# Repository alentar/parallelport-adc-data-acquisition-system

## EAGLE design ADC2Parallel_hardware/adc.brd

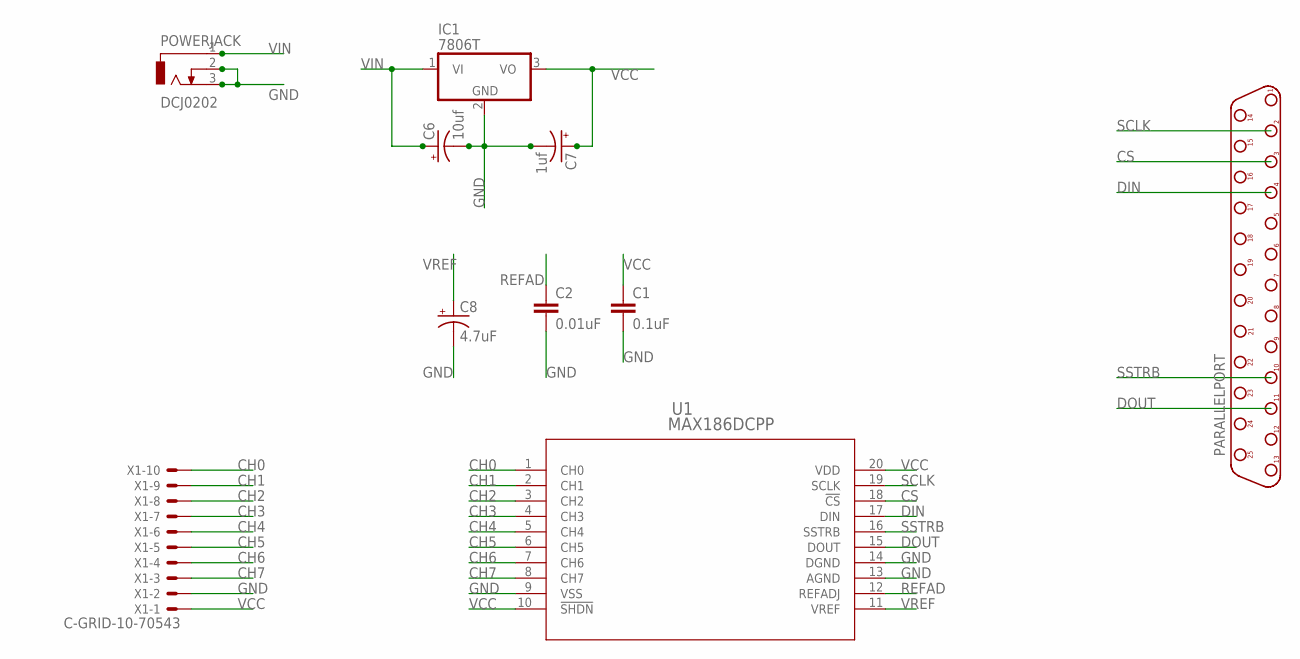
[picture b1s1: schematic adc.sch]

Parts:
C1: 0.1uF; C050-035X075
C2: 0.01uF; C050-035X075; MPN B32529C1103J189
C6: 10uf; E2-5
C7: 1uf; E2-5
C8: 4.7uF; E2-5
IC1: 7806T; TO220H
PARALLELPORT: DB25F; D-25F
POWERJACK: DCJ0202
U1: MAX186DCPP; 21-0043D_20
X1: C-GRID-10-70543; 70543-10

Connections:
CH0: U1.1 (CH0), X1.10
CH1: U1.2 (CH1), X1.9
CH2: U1.3 (CH2), X1.8
CH3: U1.4 (CH3), X1.7
CH4: U1.5 (CH4), X1.6
CH5: U1.6 (CH5), X1.5
CH6: U1.7 (CH6), X1.4
CH7: U1.8 (CH7), X1.3
CS: PARALLELPORT.3, U1.18 (!CS)
DIN: PARALLELPORT.4, U1.17 (DIN)
DOUT: PARALLELPORT.11, U1.15 (DOUT)
GND: C1.2, C2.2, C6.-, C7.-, C8.-, IC1.2 (GND), POWERJACK.2, POWERJACK.3, U1.9 (VSS), U1.13 (AGND), U1.14 (DGND), X1.2
REFAD: C2.1, U1.12 (REFADJ)
SCLK: PARALLELPORT.2, U1.19 (SCLK)
SSTRB: PARALLELPORT.10, U1.16 (SSTRB)
VCC: C1.1, C7.+, IC1.3 (VO), U1.10 (!SHDN), U1.20 (VDD), X1.1
VIN: C6.+, IC1.1 (VI), POWERJACK.1
VREF: C8.+, U1.11 (VREF)

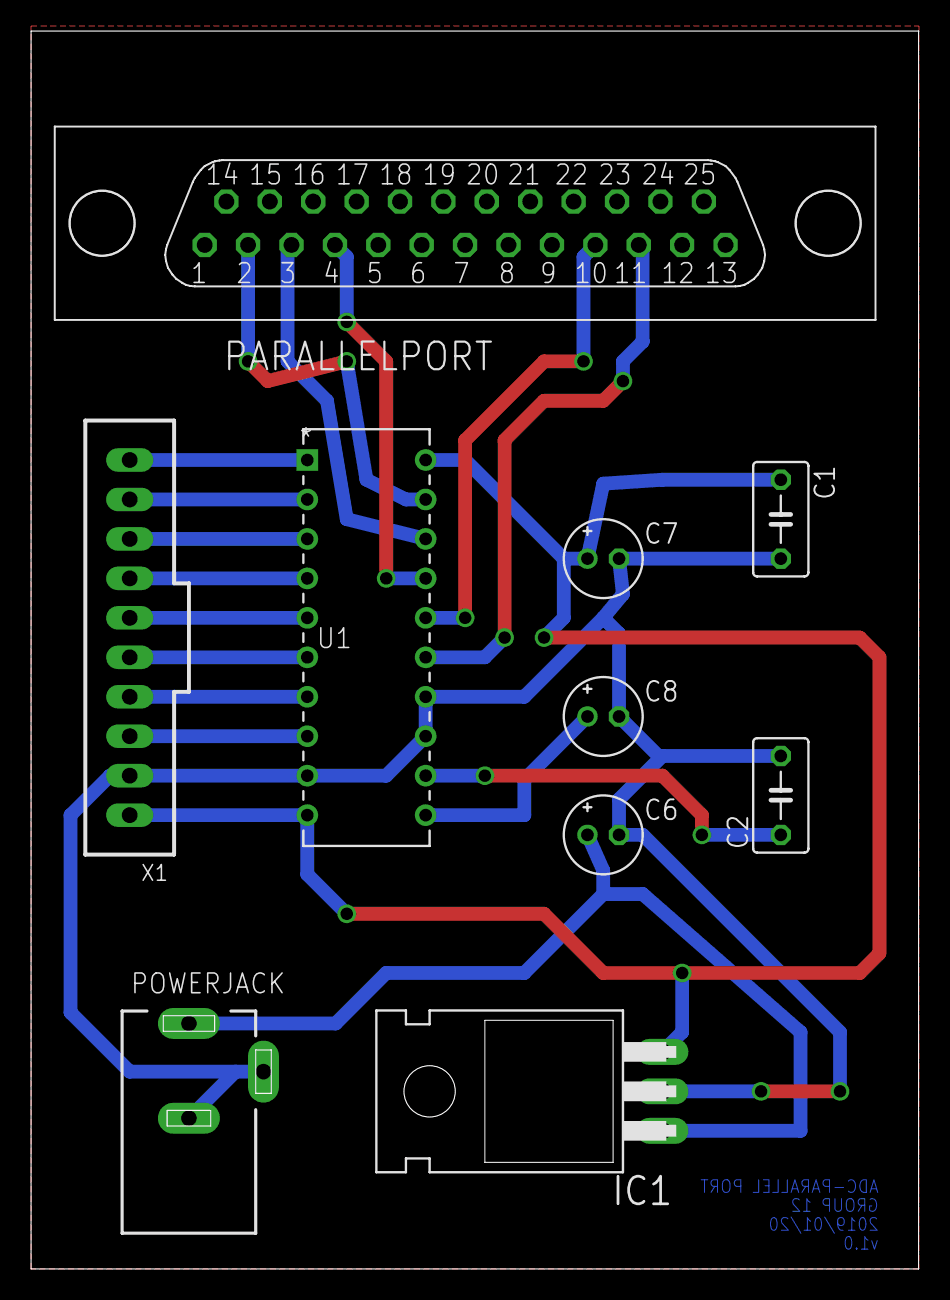
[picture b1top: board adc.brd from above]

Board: 2 copper layers, 57.1 x 79.7 mm, 10 parts (0 on the bottom side), 18 nets.

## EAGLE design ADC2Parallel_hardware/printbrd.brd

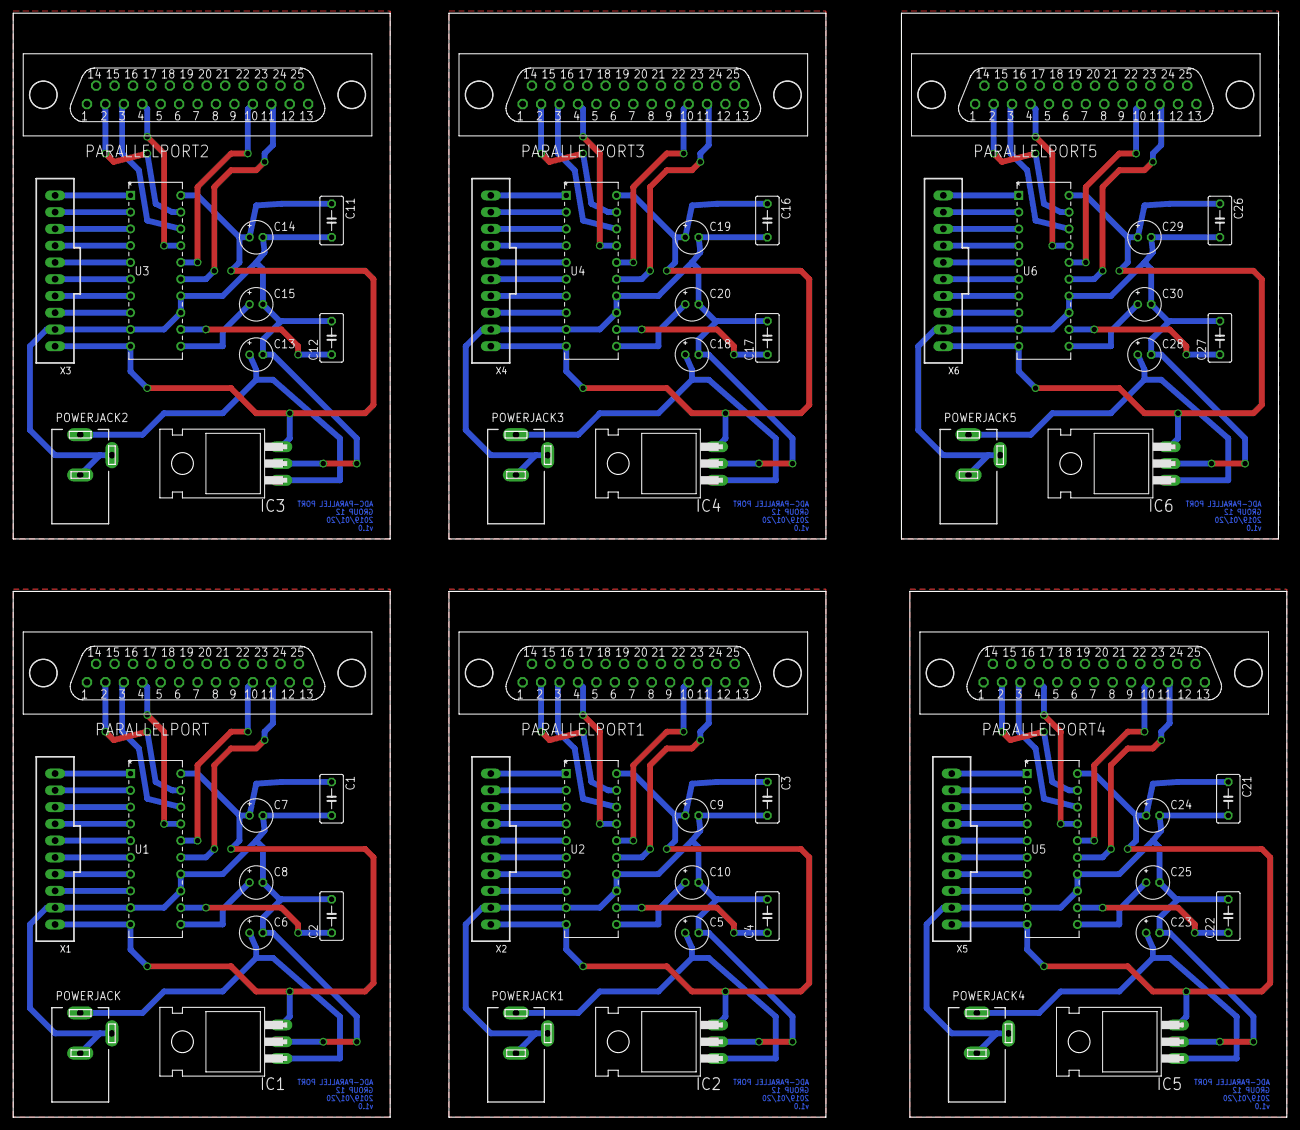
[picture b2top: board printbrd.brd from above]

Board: 2 copper layers, 193.0 x 167.3 mm, 60 parts (0 on the bottom side), 108 nets.

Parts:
C1, C3, C11, C16, C21, C26: 0.1uF; C050-035X075
C2, C4, C12, C17, C22, C27: 0.01uF; C050-035X075
C5, C6, C13, C18, C23, C28: 10uf; E2-5
C7, C9, C14, C19, C24, C29: 1uf; E2-5
C8, C10, C15, C20, C25, C30: 4.7uF; E2-5
IC1, IC2, IC3, IC4, IC5, IC6: 7806T; TO220H
PARALLELPORT, PARALLELPORT1, PARALLELPORT2, PARALLELPORT3, PARALLELPORT4, PARALLELPORT5: D-25F
POWERJACK, POWERJACK1, POWERJACK2, POWERJACK3, POWERJACK4, POWERJACK5: DCJ0202
U1, U2, U3, U4, U5, U6: MAX186DCPP; 21-0043D_20
X1, X2, X3, X4, X5, X6: C-GRID-10-70543; 70543-10

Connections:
CH0: U1.1, X1.10
CH1: U1.2, X1.9
CH2: U1.3, X1.8
CH3: U1.4, X1.7
CH4: U1.5, X1.6
CH5: U1.6, X1.5
CH6: U1.7, X1.4
CH7: U1.8, X1.3
CH8: U2.1, X2.10
CH9: U2.2, X2.9
CH10: U2.3, X2.8
CH11: U2.4, X2.7
CH12: U2.5, X2.6
CH13: U2.6, X2.5
CH14: U2.7, X2.4
CH15: U2.8, X2.3
CH16: U3.1, X3.10
CH17: U3.2, X3.9
CH18: U3.3, X3.8
CH19: U3.4, X3.7
CH20: U3.5, X3.6
CH21: U3.6, X3.5
CH22: U3.7, X3.4
CH23: U3.8, X3.3
CH24: U4.1, X4.10
CH25: U4.2, X4.9
CH26: U4.3, X4.8
CH27: U4.4, X4.7
CH28: U4.5, X4.6
CH29: U4.6, X4.5
CH30: U4.7, X4.4
CH31: U4.8, X4.3
CH32: U5.1, X5.10
CH33: U5.2, X5.9
CH34: U5.3, X5.8
CH35: U5.4, X5.7
CH36: U5.5, X5.6
CH37: U5.6, X5.5
CH38: U5.7, X5.4
CH39: U5.8, X5.3
CH40: U6.1, X6.10
CH41: U6.2, X6.9
CH42: U6.3, X6.8
CH43: U6.4, X6.7
CH44: U6.5, X6.6
CH45: U6.6, X6.5
CH46: U6.7, X6.4
CH47: U6.8, X6.3
CS: PARALLELPORT.3, U1.18
CS1: PARALLELPORT1.3, U2.18
CS2: PARALLELPORT2.3, U3.18
CS3: PARALLELPORT3.3, U4.18
CS4: PARALLELPORT4.3, U5.18
CS5: PARALLELPORT5.3, U6.18
DIN: PARALLELPORT.4, U1.17
DIN1: PARALLELPORT1.4, U2.17
DIN2: PARALLELPORT2.4, U3.17
DIN3: PARALLELPORT3.4, U4.17
DIN4: PARALLELPORT4.4, U5.17
DIN5: PARALLELPORT5.4, U6.17
DOUT: PARALLELPORT.11, U1.15
DOUT1: PARALLELPORT1.11, U2.15
DOUT2: PARALLELPORT2.11, U3.15
DOUT3: PARALLELPORT3.11, U4.15
DOUT4: PARALLELPORT4.11, U5.15
DOUT5: PARALLELPORT5.11, U6.15
GND: C1.2, C2.2, C6.-, C7.-, C8.-, IC1.2, POWERJACK.2, POWERJACK.3, U1.9, U1.13, U1.14, X1.2
GND1: C3.2, C4.2, C5.-, C9.-, C10.-, IC2.2, POWERJACK1.2, POWERJACK1.3, U2.9, U2.13, U2.14, X2.2
GND2: C11.2, C12.2, C13.-, C14.-, C15.-, IC3.2, POWERJACK2.2, POWERJACK2.3, U3.9, U3.13, U3.14, X3.2
GND3: C16.2, C17.2, C18.-, C19.-, C20.-, IC4.2, POWERJACK3.2, POWERJACK3.3, U4.9, U4.13, U4.14, X4.2
GND4: C21.2, C22.2, C23.-, C24.-, C25.-, IC5.2, POWERJACK4.2, POWERJACK4.3, U5.9, U5.13, U5.14, X5.2
GND5: C26.2, C27.2, C28.-, C29.-, C30.-, IC6.2, POWERJACK5.2, POWERJACK5.3, U6.9, U6.13, U6.14, X6.2
REFAD: C2.1, U1.12
REFAD1: C4.1, U2.12
REFAD2: C12.1, U3.12
REFAD3: C17.1, U4.12
REFAD4: C22.1, U5.12
REFAD5: C27.1, U6.12
SCLK: PARALLELPORT.2, U1.19
SCLK1: PARALLELPORT1.2, U2.19
SCLK2: PARALLELPORT2.2, U3.19
SCLK3: PARALLELPORT3.2, U4.19
SCLK4: PARALLELPORT4.2, U5.19
SCLK5: PARALLELPORT5.2, U6.19
SSTRB: PARALLELPORT.10, U1.16
SSTRB1: PARALLELPORT1.10, U2.16
SSTRB2: PARALLELPORT2.10, U3.16
SSTRB3: PARALLELPORT3.10, U4.16
SSTRB4: PARALLELPORT4.10, U5.16
SSTRB5: PARALLELPORT5.10, U6.16
VCC: C1.1, C7.+, IC1.3, U1.10, U1.20, X1.1
VCC1: C3.1, C9.+, IC2.3, U2.10, U2.20, X2.1
VCC2: C11.1, C14.+, IC3.3, U3.10, U3.20, X3.1
VCC3: C16.1, C19.+, IC4.3, U4.10, U4.20, X4.1
VCC4: C21.1, C24.+, IC5.3, U5.10, U5.20, X5.1
VCC5: C26.1, C29.+, IC6.3, U6.10, U6.20, X6.1
VIN: C6.+, IC1.1, POWERJACK.1
VIN1: C5.+, IC2.1, POWERJACK1.1
VIN2: C13.+, IC3.1, POWERJACK2.1
VIN3: C18.+, IC4.1, POWERJACK3.1
VIN4: C23.+, IC5.1, POWERJACK4.1
VIN5: C28.+, IC6.1, POWERJACK5.1
VREF: C8.+, U1.11
VREF1: C10.+, U2.11
VREF2: C15.+, U3.11
VREF3: C20.+, U4.11
VREF4: C25.+, U5.11
VREF5: C30.+, U6.11

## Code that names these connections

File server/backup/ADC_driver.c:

/*------------------- ADC_driver -----------------------------------

  PURPOSE - Gives ten sensor readings over 10 seconds.
  

  COMPILE to binary st as below-
            gcc -o run_ADC ADC_driver.c

  RUN       ./lp_tty_start ./ADC_driver
*/

#include <sys/io.h>
#include <sys/time.h>
#include <stdio.h>

//------- Parallel port data.
static short lp_base_addr; // save base addr of pp port.
#define status_offset 1
#define control_offset 2
#define high 1
#define low 0

static char save_data; // save of original values.
static char save_control;
static char image_data; // use image as master record of port.
static char image_control;

int count; // used for clock data in or out

//-------Parallel port pins-------------------------
#define SCLK1 0x01
#define CS1 0x02
#define SCLK1_CS1 0x03
#define DIN1 0x04
#define DIN1_SCLK1 0x05
#define DIN1_SCLK1_CS1 0x07
#define all_low 0x00

//-------Control Byte-------------------------------
int thermo1_DIN[8] = {1, 0, 0, 0, 1, 0, 1, 0};

//-------12 bit Output------------------------------
int DOUT = 0;

//=================== pp routines ================================

//-------- lp_init() --------------------------------------------
//
// PURPOSE - given lp numb er 0-2, get lp base address,
//           save registers, disable interrupts.

void lp_init(short lp_num)
{
  switch (lp_num)
  {
  case 2:
    lp_base_addr = 0x3BC;
    break;
  case 1:
    lp_base_addr = 0x278;
    break;
  default:
    lp_base_addr = 0x378;
    break;
  }
  image_data = save_data = inb(lp_base_addr);
  image_control = save_control = inb(lp_base_addr + 2);
  outb((image_control &= 0xEF), lp_base_addr + control_offset);
}

//--------- lp_restore() ----------------------------------------
//
// PURPOSE - restore lp port to previous state.

void lp_restore()
{
  outb(save_data, lp_base_addr);
  outb(save_control, lp_base_addr + control_offset);
}

//---------check SSTRB pin------------------------------
//PURPOSE - check the SSTRB pin (pin 10 or S6)

int check_SSTRB_pin()
{
  if (inb(lp_base_addr + status_offset) & 0x40)
    return (high);
  else
    return (low);
}

//---------check DOUT pin------------------------------
//PURPOSE - check the SSTRB pin (pin 11 or S7)

int check_DOUT_pin()
{
  if (inb(lp_base_addr + status_offset) & 0x80)
    return (low);
  else
    return (high);
}

//---------two power of-----------------------------
//PURPOSE - to output two to the power of (x) - 2^x

int twopowerof(int x)
{
  int tempPow = 0;
  int value = 1;
  while (x > tempPow)
  {
    value = 2 * value;
    tempPow++;
  }
  return (value);
}

//---------Clock in 8bits------------------------------
//PURPOSE - clock in the 8 bit command into the ADC.*/

void clock_in_8bits(int buffDIN[8])
{
  for (count = 0; count <= 7; count++)
  {
    //---falling edge-------------------------
    if (buffDIN[count] == 1)
    {
      outb(DIN1, lp_base_addr); //SCLK-low, DIN-high
    }
    else
    {
      outb(all_low, lp_base_addr); //SCLK-low, DIN-low
    }

    //---rising edge---------------------------
    if (buffDIN[count] == 1)
    {
      if (count == 8)
        outb(DIN1_SCLK1_CS1, lp_base_addr);
      else
        outb(DIN1_SCLK1, lp_base_addr); //SCLK-high, DIN-high
    }
    else
    {
      if (count == 8)
        outb(SCLK1_CS1, lp_base_addr);
      else
        outb(SCLK1, lp_base_addr); //SCLK-high, DIN-low
    }
  }

  outb(CS1, lp_base_addr); //last falling edge so CS goes high
}

//---------Clock out signal-----------------------------
//PURPOSE - once tconv is finished clock out the 12 bit
//          signal from ADC

int clock_out_signal()
{
  int tempOut[12] = {0, 0, 0, 0, 0, 0, 0, 0, 0, 0, 0, 0};

  for (count = 1; count <= 14; count++)
  {
    //-----begin clocking out out byte----
    outb(0, lp_base_addr); //force pin2 SCLK to low

    //----rising edge------
    if (count == 1 && check_DOUT_pin() != 0)
    {
    }

    if (count >= 2 && count <= 13)
    {
      if (check_DOUT_pin() == high)
        tempOut[count - 2] = 1;
      else
        tempOut[count - 2] = 0;
    }

    outb(SCLK1, lp_base_addr); //force pin2 SCLK to high
  }

  outb(0, lp_base_addr); //force pin2 SCLK to low
  int dec = 0;
  for (count = 0; count <= 11; count++)
  {
    dec = ((tempOut[11 - count]) * (twopowerof(count))) + dec;
  }

  return (dec);
}

//---------get thermistor sensor reading-----------------------
//PURPOSE - to clock in thermistor sensor config and then clock out
//          the thermistor sensor reading as a integer.

void get_thermo1_sensor_reading()
{                          //--- begin clocking in 8 bit command/
  outb(CS1, lp_base_addr); //force CS (D2) high rest of the pins are low

  //---starting 8-bit command---
  outb(all_low, lp_base_addr); //make all pins low
  outb(DIN1, lp_base_addr);    //input DIN START(high) bit
  clock_in_8bits(thermo1_DIN); //clocking in the 8 bit command
  DOUT = clock_out_signal();   //clocking out 12 bit signal from ADC
}

//========== main ===============================================

int main(void)
{ //====== inits.
  lp_init(0);

  //--- initialize primary time interval PTI timer.
  struct timespec sleep_time;
  sleep_time.tv_sec = 0;
  sleep_time.tv_nsec = 0; // 10 ms PTI.

  //--- output the sensor reading every second x 10 times
  int i;
  for (i = 0; i < 10; i++)
  {
    get_thermo1_sensor_reading();
    if (DOUT == 4095)
      printf("ERROR: No power or connection \n");
    else
      printf("Voltage Reading: %d \n", DOUT);
    sleep(1);
  }

  printf("********************************************\n");

  lp_restore();
  return (0);
}

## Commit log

2019-01-20 client init
2019-01-20 driver
2019-01-20 close on yes
2019-01-20 sync
2019-01-21 eventbus resource manager
2019-01-21 basic connection
2019-01-21 GraphView Streams
2019-01-22 typo
2019-02-05 added scripting
2019-02-19 server update
2019-02-19 new icons
2019-02-19 stream manager linux api
2019-02-19 graph editor
2019-02-19 some changes
2019-02-19 hardware design :rocket:
    hardware design file added
2019-02-19 issue fixed
2019-02-19 stdlib
2019-02-20 some
